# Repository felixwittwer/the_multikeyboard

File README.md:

<div align="center">

# the_multikeyboard

</div>

A custom keyboard that does it all. Standard keyboard, steno keyboard and macropad. It is a 115% keyboard that is a true alrounder. Besides all the features it excells your typing experience by having a slightly curved shape and some cool wrist rests that attatch magneticaly.

## About the project

I am actually someone that is currently learning steno myself and I already have a matching keyboard for that. Besides I also have a Macropad and of course a normal keyboard. You counted right I have three keyboards on my desk and this is bothering me. Thats why I decided to build my first own custom keyboard that combines all three. **THE MULTIKEYBOARD** is a keyboard that consists of a macropad (on the right side), a full sized keyboard (everything else :]) and a section in the middle that can be used for stenography typing.

[Look at some cool renders ](#renders) 

[... some CAD](#cad)

[... all the nice features](#features)

[... the PCB](#pcb-and-schematics)

[... the firmware](#firmware)

[... all the parst you need (BOM)](#bom)

## The project

### Renders

### CAD

### Features

**magnetic wrist rest**

Magnets are getting pressed into their location on the keyboard side and get clamped down by the crews holding the top and bottom piece of the keyboard together. On the wrist rest side the magnets just get glued into place. This designvhoice was intentional. I knwo that it is possible to encase magntes by pausing your 3D printer and the resuming but the case is already difficula enough to print due to its size so I don't wanted to add another hurdel.

**OLED**

The keyboard also has a small 0.91" OLED screen that tells you which layer you are currently using. In the future I will maybee add some small pixelart.

**dials with knurling**

The left side of the keyboard is basically a macropad with 16 kustomizable keys and two rotary encoders witha custom dial. The knurling on the dials is probably going to feel amazing.

**steno capabilities**

I intentionally designed the kyboard to be steno capable and also have a layout that could fita steno keyboard.

(blue -> macropad, magenta -> steno, green -> numpad)

### PCB and schematics

## Firmware

The keyboard is running KMK have a look [here](/firmware/).

## BOM

**sum: 79.67 USD**

| part name | amount | price | link | note |
| --------- | ------ | ----- | ---- | ---- |
| Rotary encoder EC24 | 2 | 1.32 USD | https://de.aliexpress.com/item/1005006894514858.html?spm=a2g0o.productlist.main.2.7f3151dbLgFP04&algo_pvid=9129263f-29b5-45c7-9270-6505827be216&pdp_ext_f=%7B%22order%22%3A%2212%22%2C%22eval%22%3A%221%22%7D&utparam-url=scene%3Asearch%7Cquery_from%3A | look out for the EC numer it is importent for the resolution of the encoder 
| Keyswitches | 120 (54+66) | 21.12 USD | https://de.aliexpress.com/item/1005006091988869.html?spm=a2g0o.productlist.main.11.54f5116676VXSy&algo_pvid=5683f259-8333-46de-8018-3bd4b785d0da&pdp_ext_f=%7B%22order%22%3A%22205%22%2C%22eval%22%3A%221%22%7D&utparam-url=scene%3Asearch%7Cquery_from%3A
| Keycaps | 120 (54+66) | 7.88 USD| https://de.aliexpress.com/item/32842379355.html?spm=a2g0o.productlist.main.13.19dd3939CSNGEC&algo_pvid=53737e4f-6131-4c20-955c-c0b48daf2625&pdp_ext_f=%7B%22order%22%3A%2286%22%2C%22eval%22%3A%221%22%7D&utparam-url=scene%3Asearch%7Cquery_from%3A | please look where you can buy matching quantities 120 Keys is larger than normal keyboard size
| hotswap socets | 120 (54+66) | 12.92 USD | https://de.aliexpress.com/item/1005007476614771.html?gatewayAdapt=glo2deu | ---- |
| diodes SOD-123 | 120 (54+66) | 2.74 USD | https://de.aliexpress.com/item/1005004664827360.html?spm=a2g0o.productlist.main.2.730d3027Xsqwva&algo_pvid=82ad0fed-5a2a-47ba-b2ca-b1062569d1e1&pdp_ext_f=%7B%22order%22%3A%2215%22%2C%22eval%22%3A%221%22%7D&utparam-url=scene%3Asearch%7Cquery_from%3A | ---- |
| headphone jack | 2pcs | 1.16 USD | https://de.aliexpress.com/item/4000661908135.html?spm=a2g0o.productlist.main.6.13bb1c8aFr9YPX&algo_pvid=a0e2646d-b512-4a32-a7a1-672e32ca9da6&pdp_ext_f=%7B%22order%22%3A%22166%22%2C%22eval%22%3A%221%22%7D&utparam-url=scene%3Asearch%7Cquery_from%3A | ---- |
| magnets 10mmx2mm | 8 | 1.16 USD | https://de.aliexpress.com/item/1005009238165372.html?spm=a2g0o.productlist.main.5.22047957vqqfP9&algo_pvid=c622bad2-8ed7-4326-9252-e0228163b2aa&pdp_ext_f=%7B%22order%22%3A%22599%22%2C%22eval%22%3A%221%22%7D&utparam-url=scene%3Asearch%7Cquery_from%3A | ---- |
| ESP32-S3 | 2 | 15.12 USD | https://de.aliexpress.com/item/1005008209644199.html?spm=a2g0o.productlist.main.2.450b6619Wqsygq&algo_pvid=b6d6b6cd-dfe1-4b51-a066-5df1bfd08fe2&pdp_ext_f=%7B%22order%22%3A%2263%22%2C%22eval%22%3A%221%22%7D&utparam-url=scene%3Asearch%7Cquery_from%3A | ---- |
| 0.96" OLED | 1 | 1.16 USD | https://de.aliexpress.com/item/1005006153887805.html?spm=a2g0o.productlist.main.4.78c6NVUJNVUJnM&aem_p4p_detail=20250731095618221437588698900003594592&algo_pvid=1ea1ca72-3c62-47c2-bed4-becdd3fbee01&pdp_ext_f=%7B%22order%22%3A%2293%22%2C%22eval%22%3A%221%22%7D&utparam-url=scene%3Asearch%7Cquery_from%3A&search_p4p_id=20250731095618221437588698900003594592_1 | ---- |
| PCB LEFT Main | 1 | ~ 5 USD |  https://jlcpcb.com/ | price is subject to JLCs review |
| PCB RIGHT BACK | 1 | ~ 5 USD |  https://jlcpcb.com/ | price is subject to JLCs review |
| | total | 74.67 + (shipping ~5 USD) **79.67 USD** | 

**sum: 79.67 USD**

## Credits

**Thanks for the detailed 3D models!**

Gateron keyswitch 3D model: https://www.gateron.com/pages/3d

Keycap 3D model: https://grabcad.com/library/dsa-keycap-for-cherry-mx-switches-1

ESP32-S3 (before I modified it): https://grabcad.com/library/esp32-s3-module-for-pcb-preview-1

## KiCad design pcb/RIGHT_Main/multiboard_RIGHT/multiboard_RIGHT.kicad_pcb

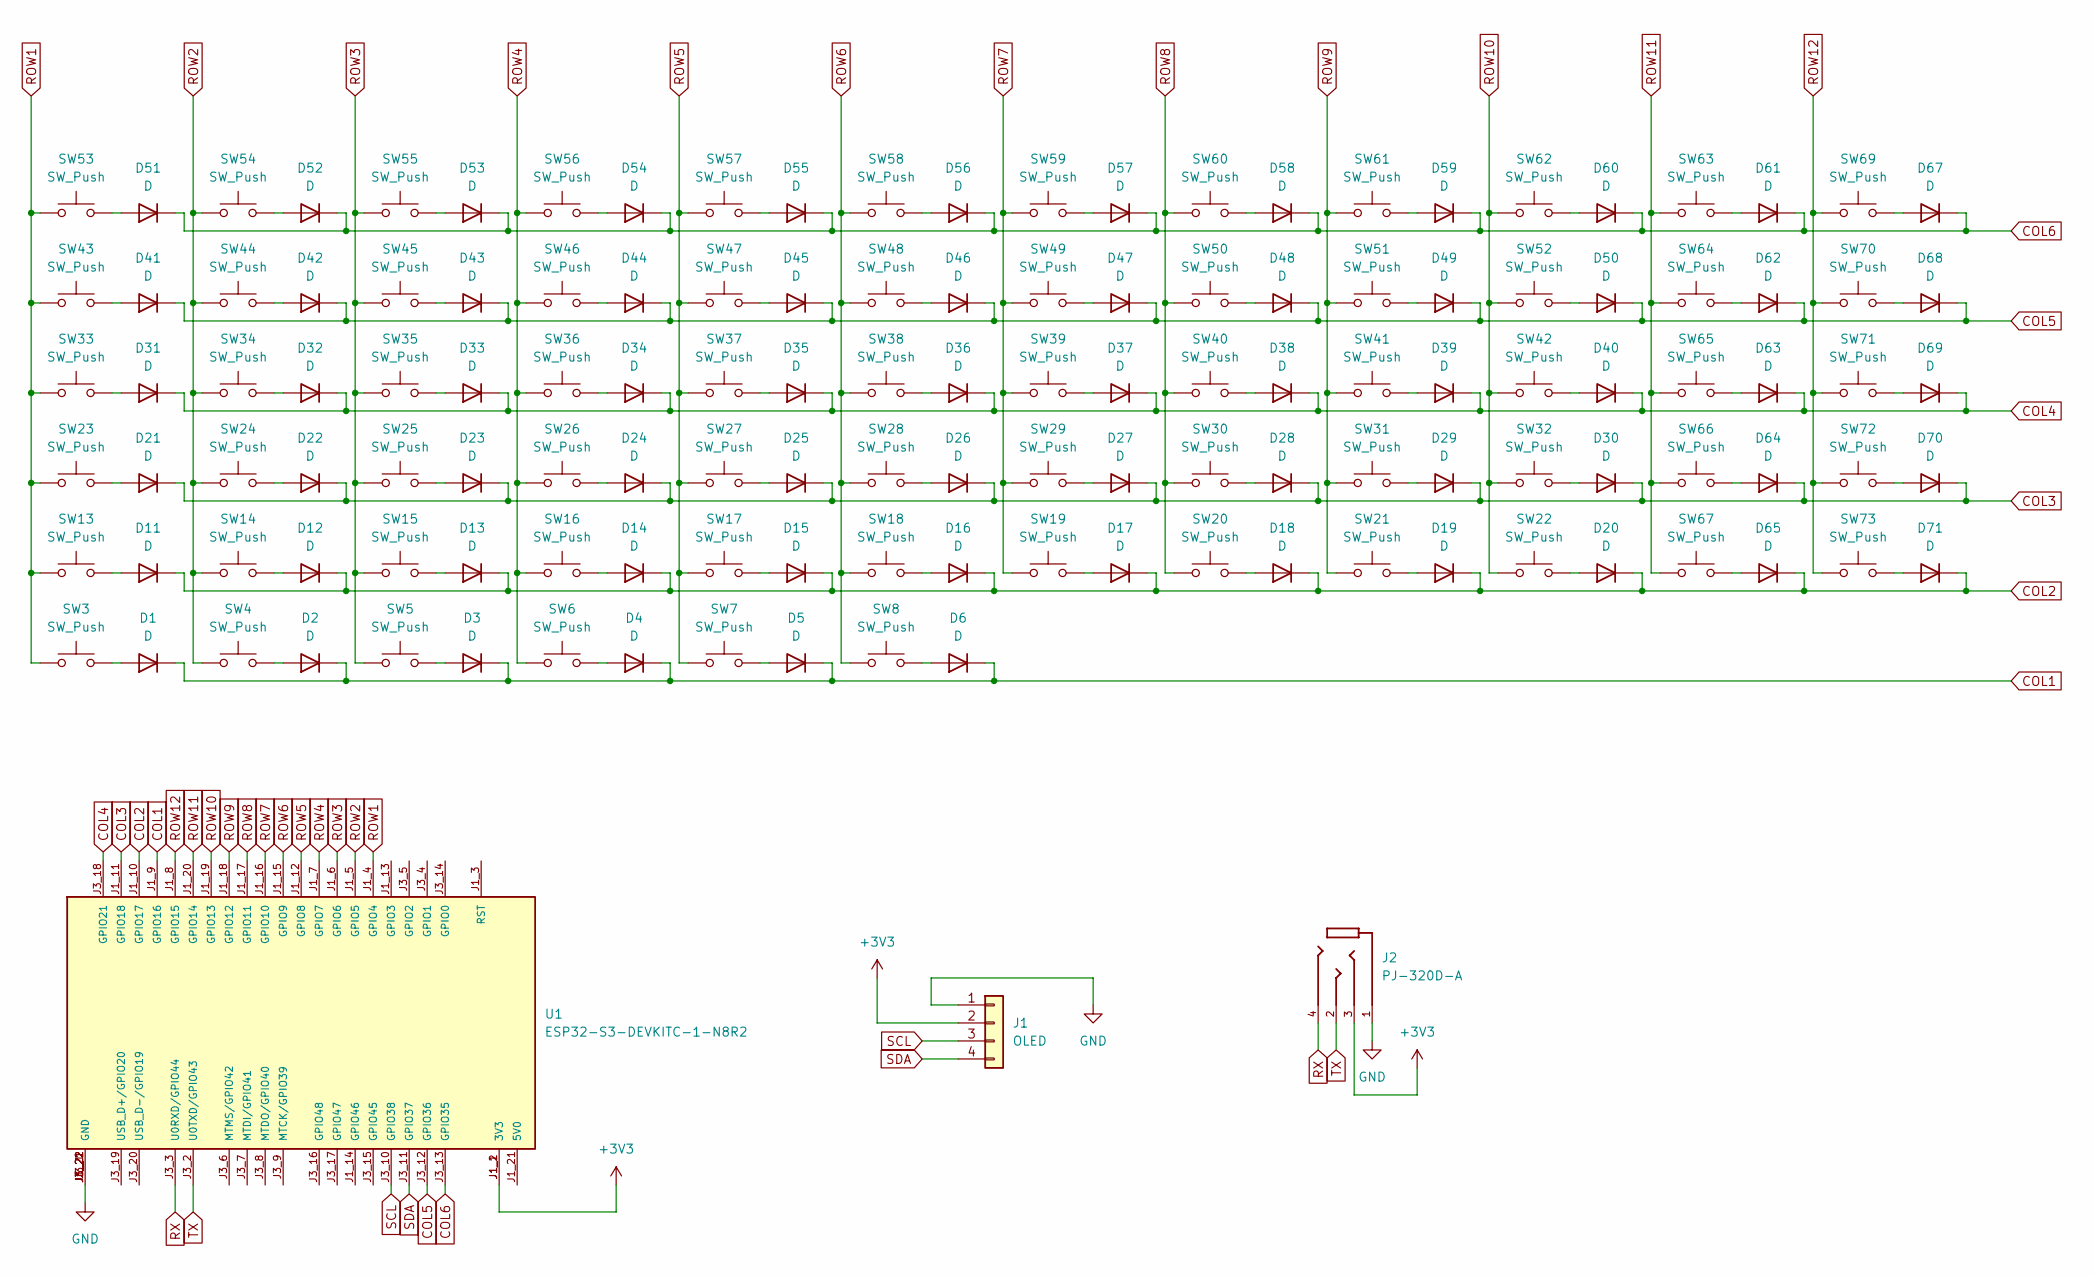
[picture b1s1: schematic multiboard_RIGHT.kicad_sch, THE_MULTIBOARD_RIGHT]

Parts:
D1, D2, D3, D4, D5, D6, D11, D12, D13, D14, D15, D16, D17, D18, D19, D20, D21, D22, D23, D24, D25, D26, D27, D28, D29, D30, D31, D32, D33, D34, D35, D36, D37, D38, D39, D40, D41, D42, D43, D44, D45, D46, D47, D48, D49, D50, D51, D52, D53, D54, D55, D56, D57, D58, D59, D60, D61, D62, D63, D64, D65, D67, D68, D69, D70, D71: D; D_SOD-123
J1: OLED; PinSocket_1x04_P2.54mm_Vertical
J2: PJ-320D-A; HRO_PJ-320D-A; PARTREV B
SW3, SW4, SW5, SW6, SW7, SW8, SW13, SW14, SW15, SW16, SW17, SW18, SW19, SW20, SW21, SW22, SW23, SW24, SW25, SW26, SW27, SW28, SW29, SW30, SW31, SW32, SW33, SW34, SW35, SW36, SW37, SW38, SW39, SW40, SW41, SW42, SW43, SW44, SW45, SW46, SW47, SW48, SW49, SW50, SW51, SW52, SW53, SW54, SW55, SW56, SW57, SW58, SW59, SW60, SW61, SW62, SW63, SW64, SW65, SW66, SW67, SW69, SW70, SW71, SW72, SW73: SW_Push; MX-Hotswap-1U
U1: ESP32-S3-DEVKITC-1-N8R2; XCVR_ESP32-S3-DEVKITC-1-N8R2; PARTREV V1

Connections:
+3V3: J1.2, J2.3, U1.J1_1 (3V3), U1.J1_2 (3V3)
COL1: D1.1 (K), D2.1 (K), D3.1 (K), D4.1 (K), D5.1 (K), D6.1 (K), U1.J1_9 (GPIO16)
COL2: D11.1 (K), D12.1 (K), D13.1 (K), D14.1 (K), D15.1 (K), D16.1 (K), D17.1 (K), D18.1 (K), D19.1 (K), D20.1 (K), D65.1 (K), D71.1 (K), U1.J1_10 (GPIO17)
COL3: D21.1 (K), D22.1 (K), D23.1 (K), D24.1 (K), D25.1 (K), D26.1 (K), D27.1 (K), D28.1 (K), D29.1 (K), D30.1 (K), D64.1 (K), D70.1 (K), U1.J1_11 (GPIO18)
COL4: D31.1 (K), D32.1 (K), D33.1 (K), D34.1 (K), D35.1 (K), D36.1 (K), D37.1 (K), D38.1 (K), D39.1 (K), D40.1 (K), D63.1 (K), D69.1 (K), U1.J3_18 (GPIO21)
COL5: D41.1 (K), D42.1 (K), D43.1 (K), D44.1 (K), D45.1 (K), D46.1 (K), D47.1 (K), D48.1 (K), D49.1 (K), D50.1 (K), D62.1 (K), D68.1 (K), U1.J3_12 (GPIO36)
COL6: D51.1 (K), D52.1 (K), D53.1 (K), D54.1 (K), D55.1 (K), D56.1 (K), D57.1 (K), D58.1 (K), D59.1 (K), D60.1 (K), D61.1 (K), D67.1 (K), U1.J3_13 (GPIO35)
GND: J1.1, J2.1, U1.J1_22 (GND), U1.J3_1 (GND), U1.J3_21 (GND), U1.J3_22 (GND)
unnamed: D1.2 (A), SW3.2
unnamed: D2.2 (A), SW4.2
unnamed: D3.2 (A), SW5.2
unnamed: D4.2 (A), SW6.2
unnamed: D5.2 (A), SW7.2
unnamed: D6.2 (A), SW8.2
unnamed: D11.2 (A), SW13.2
unnamed: D12.2 (A), SW14.2
unnamed: D13.2 (A), SW15.2
unnamed: D14.2 (A), SW16.2
unnamed: D15.2 (A), SW17.2
unnamed: D16.2 (A), SW18.2
unnamed: D17.2 (A), SW19.2
unnamed: D18.2 (A), SW20.2
unnamed: D19.2 (A), SW21.2
unnamed: D20.2 (A), SW22.2
unnamed: D21.2 (A), SW23.2
unnamed: D22.2 (A), SW24.2
unnamed: D23.2 (A), SW25.2
unnamed: D24.2 (A), SW26.2
unnamed: D25.2 (A), SW27.2
unnamed: D26.2 (A), SW28.2
unnamed: D27.2 (A), SW29.2
unnamed: D28.2 (A), SW30.2
unnamed: D29.2 (A), SW31.2
unnamed: D30.2 (A), SW32.2
unnamed: D31.2 (A), SW33.2
unnamed: D32.2 (A), SW34.2
unnamed: D33.2 (A), SW35.2
unnamed: D34.2 (A), SW36.2
unnamed: D35.2 (A), SW37.2
unnamed: D36.2 (A), SW38.2
unnamed: D37.2 (A), SW39.2
unnamed: D38.2 (A), SW40.2
unnamed: D39.2 (A), SW41.2
unnamed: D40.2 (A), SW42.2
unnamed: D41.2 (A), SW43.2
unnamed: D42.2 (A), SW44.2
unnamed: D43.2 (A), SW45.2
unnamed: D44.2 (A), SW46.2
unnamed: D45.2 (A), SW47.2
unnamed: D46.2 (A), SW48.2
unnamed: D47.2 (A), SW49.2
unnamed: D48.2 (A), SW50.2
unnamed: D49.2 (A), SW51.2
unnamed: D50.2 (A), SW52.2
unnamed: D51.2 (A), SW53.2
unnamed: D52.2 (A), SW54.2
unnamed: D53.2 (A), SW55.2
unnamed: D54.2 (A), SW56.2
unnamed: D55.2 (A), SW57.2
unnamed: D56.2 (A), SW58.2
unnamed: D57.2 (A), SW59.2
unnamed: D58.2 (A), SW60.2
unnamed: D59.2 (A), SW61.2
unnamed: D60.2 (A), SW62.2
unnamed: D61.2 (A), SW63.2
unnamed: D62.2 (A), SW64.2
unnamed: D63.2 (A), SW65.2
unnamed: D64.2 (A), SW66.2
unnamed: D65.2 (A), SW67.2
unnamed: D67.2 (A), SW69.2
unnamed: D68.2 (A), SW70.2
unnamed: D69.2 (A), SW71.2
unnamed: D70.2 (A), SW72.2
unnamed: D71.2 (A), SW73.2
ROW1: SW3.1, SW13.1, SW23.1, SW33.1, SW43.1, SW53.1, U1.J1_4 (GPIO4)
ROW2: SW4.1, SW14.1, SW24.1, SW34.1, SW44.1, SW54.1, U1.J1_5 (GPIO5)
ROW3: SW5.1, SW15.1, SW25.1, SW35.1, SW45.1, SW55.1, U1.J1_6 (GPIO6)
ROW4: SW6.1, SW16.1, SW26.1, SW36.1, SW46.1, SW56.1, U1.J1_7 (GPIO7)
ROW5: SW7.1, SW17.1, SW27.1, SW37.1, SW47.1, SW57.1, U1.J1_12 (GPIO8)
ROW6: SW8.1, SW18.1, SW28.1, SW38.1, SW48.1, SW58.1, U1.J1_15 (GPIO9)
ROW7: SW19.1, SW29.1, SW39.1, SW49.1, SW59.1, U1.J1_16 (GPIO10)
ROW8: SW20.1, SW30.1, SW40.1, SW50.1, SW60.1, U1.J1_17 (GPIO11)
ROW9: SW21.1, SW31.1, SW41.1, SW51.1, SW61.1, U1.J1_18 (GPIO12)
ROW10: SW22.1, SW32.1, SW42.1, SW52.1, SW62.1, U1.J1_19 (GPIO13)
ROW11: SW63.1, SW64.1, SW65.1, SW66.1, SW67.1, U1.J1_20 (GPIO14)
ROW12: SW69.1, SW70.1, SW71.1, SW72.1, SW73.1, U1.J1_8 (GPIO15)
RX: J2.4, U1.J3_3 (U0RXD/GPIO44)
SCL: J1.3, U1.J3_10 (GPIO38)
SDA: J1.4, U1.J3_11 (GPIO37)
TX: J2.2, U1.J3_2 (U0TXD/GPIO43)

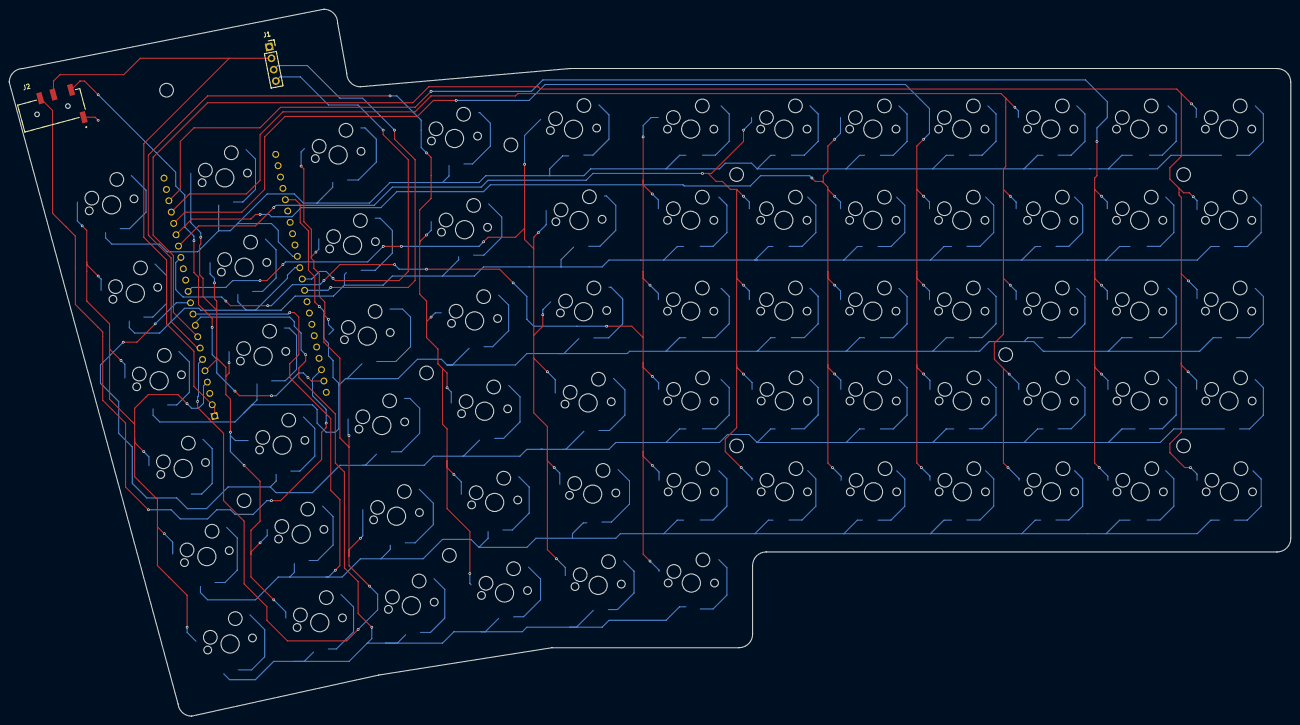
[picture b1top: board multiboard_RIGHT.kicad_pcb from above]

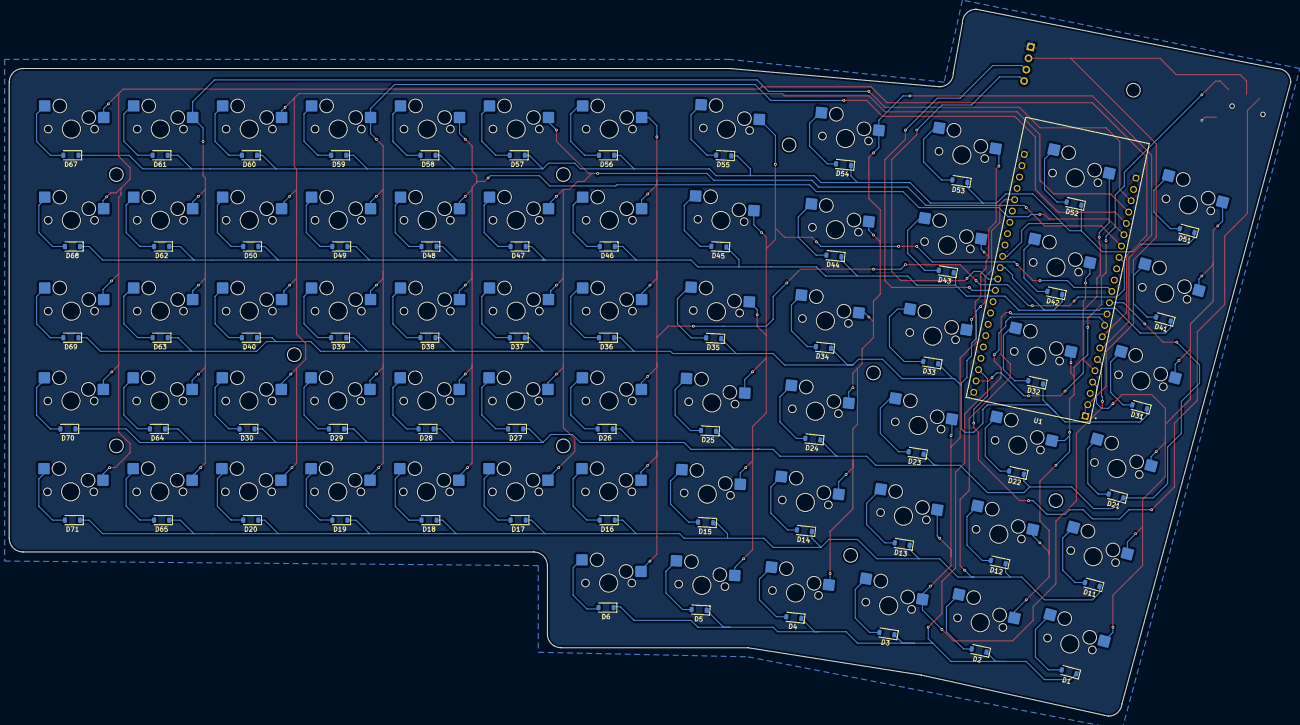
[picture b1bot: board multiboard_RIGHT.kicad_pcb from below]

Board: 2 copper layers, 281.0 x 155.0 mm, 135 parts (133 on the bottom side), 90 nets.

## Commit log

2025-07-29 add rough layout of split keyboard
2025-07-29 add schematics for LEFT PCB
2025-07-30 finishing LEFT PCB
2025-07-30 finish left and right main pcbs
2025-07-31 add cad files
2025-07-31 add firmware
2025-07-31 add headphone jack
2025-07-31 getting ready for submission - add production files - refine BOM - make README beautiful
2025-07-31 Update README.md
    Typo
